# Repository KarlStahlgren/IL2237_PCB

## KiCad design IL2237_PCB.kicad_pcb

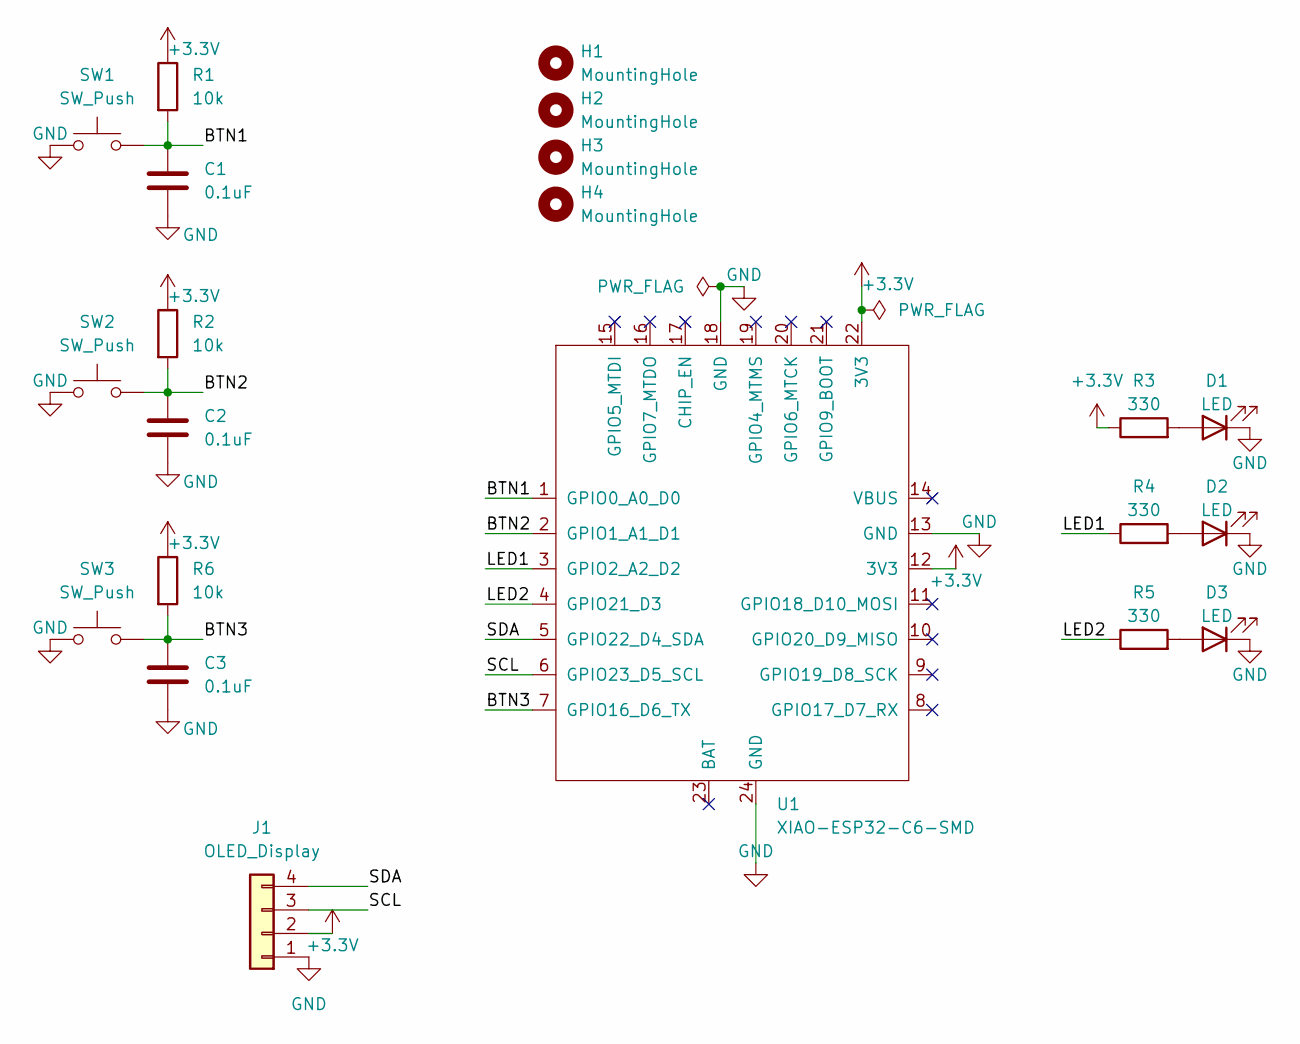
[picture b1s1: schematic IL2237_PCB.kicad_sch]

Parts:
C1, C2, C3: 0.1uF; C_Disc_D5.0mm_W2.5mm_P2.50mm
D1, D2, D3: LED; LED_D5.0mm
H1, H2, H3, H4: MountingHole; MountingHole_2.5mm_Pad
J1: OLED_Display; PinHeader_1x04_P2.54mm_Vertical
R1, R2, R6: 10k; R_Axial_DIN0207_L6.3mm_D2.5mm_P7.62mm_Horizontal
R3, R4, R5: 330; R_Axial_DIN0207_L6.3mm_D2.5mm_P7.62mm_Horizontal
SW1, SW2, SW3: SW_Push; SW_PUSH_6mm
U1: XIAO-ESP32-C6-SMD

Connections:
+3.3V: J1.2, R1.1, R2.1, R3.1, R6.1, U1.12 (3V3), U1.22 (3V3)
/BTN1: C1.1, R1.2, SW1.2, U1.1 (GPIO0_A0_D0)
/BTN2: C2.1, R2.2, SW2.2, U1.2 (GPIO1_A1_D1)
/BTN3: C3.1, R6.2, SW3.2, U1.7 (GPIO16_D6_TX)
/LED1: R4.1, U1.3 (GPIO2_A2_D2)
/LED2: R5.1, U1.4 (GPIO21_D3)
/SCL: J1.3, U1.6 (GPIO23_D5_SCL)
/SDA: J1.4, U1.5 (GPIO22_D4_SDA)
GND: C1.2, C2.2, C3.2, D1.1 (K), D2.1 (K), D3.1 (K), J1.1, SW1.1, SW2.1, SW3.1, U1.13 (GND), U1.18 (GND), U1.24 (GND)
unnamed: D1.2 (A), R3.2
unnamed: D2.2 (A), R4.2
unnamed: D3.2 (A), R5.2

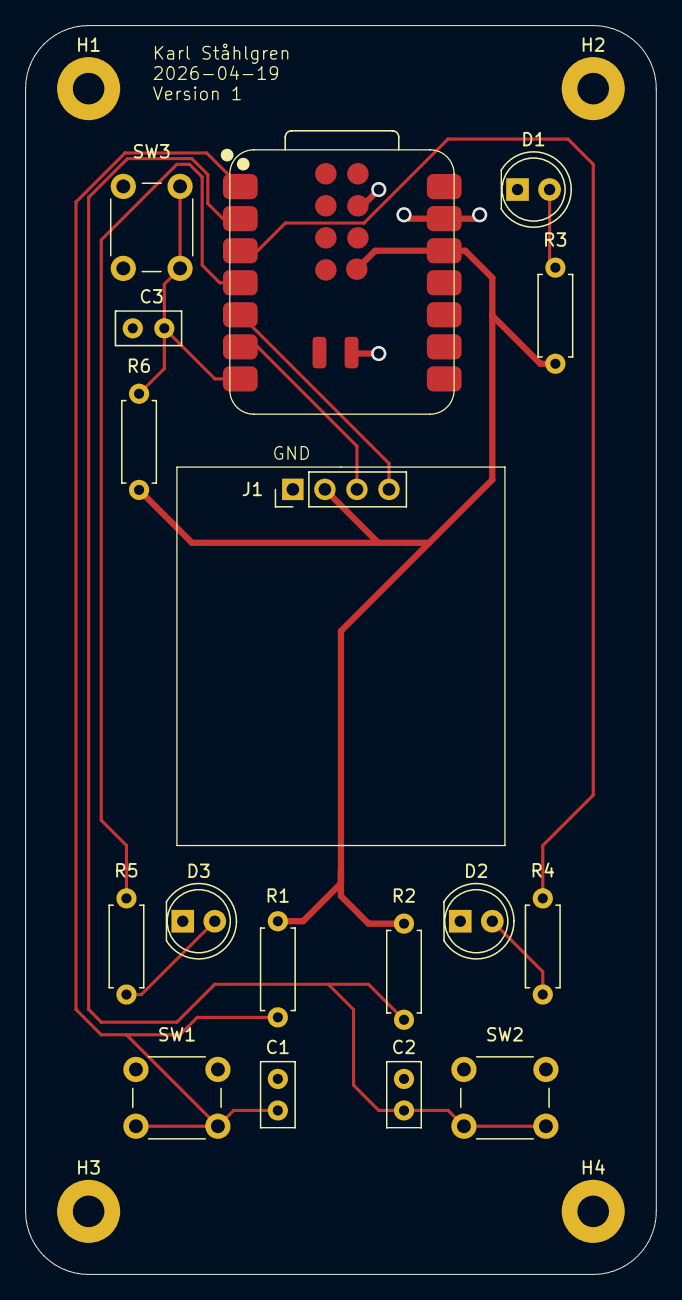
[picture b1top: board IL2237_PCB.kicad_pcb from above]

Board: 2 copper layers, 50.0 x 99.0 mm, 21 parts (0 on the bottom side), 12 nets.

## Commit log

2026-04-19 finished routing
